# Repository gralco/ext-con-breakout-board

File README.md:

A breakout board for J10 on the Librem 5.

The rigid section has an overall thickness of 1.2mm, the flex section has an overall thickness of flex section is 0.126mm, and the stiffener and its adhesive adds 0.125mm on top of the thickness of the flex.

The panels were made by PCBWay, if you would like to order these yourself then you can use their product number W159429AS1D27 to reorder the same panel.

The FPC connector used is either Panasonic AXT624124 or OK-06M024-04.

Here is a photo of a v0.6 panel:

Here is a photo of the rigid-flex board mounted inside a Librem 5, using the center M.2 cover screw to fasten the rigid section down:

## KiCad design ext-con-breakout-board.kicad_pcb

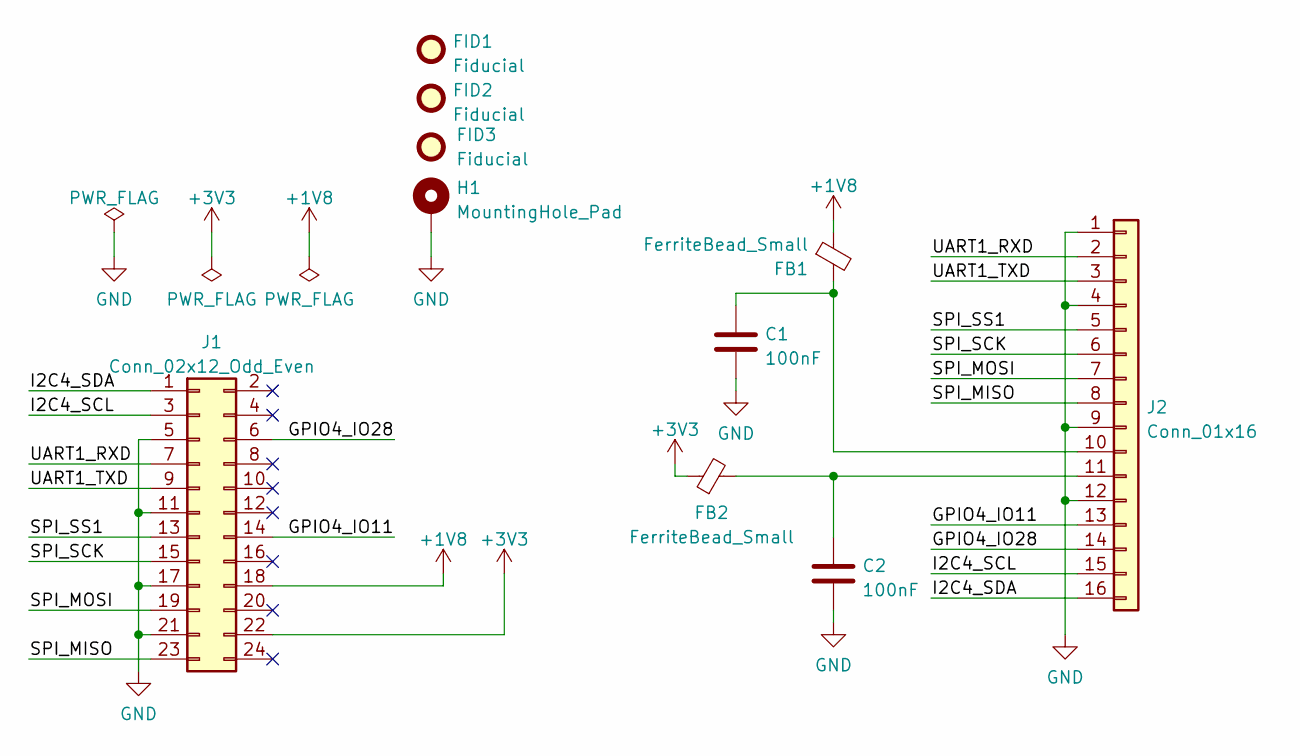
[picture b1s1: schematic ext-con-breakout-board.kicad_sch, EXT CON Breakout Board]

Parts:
C1, C2: 100nF; C_0402_1005Metric
FB1, FB2: FerriteBead_Small; L_0402_1005Metric
FID1, FID2, FID3: Fiducial; Fiducial_0.5mm_Mask1mm
H1: MountingHole_Pad; MountingHole_1.7mm_M1.4_Pad
J1: Conn_02x12_Odd_Even; AXT624124; MFG Part Num AXT624124
J2: Conn_01x16; PinHeader_1x16_P2.54mm_Vertical

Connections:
+1V8: FB1.1, J1.18
+3V3: FB2.1, J1.22
/GPIO4_IO11: J1.14, J2.13
/GPIO4_IO28: J1.6, J2.14
/I2C4_SCL: J1.3, J2.15
/I2C4_SDA: J1.1, J2.16
/SPI_MISO: J1.23, J2.8
/SPI_MOSI: J1.19, J2.7
/SPI_SCK: J1.15, J2.6
/SPI_SS1: J1.13, J2.5
/UART1_RXD: J1.7, J2.2
/UART1_TXD: J1.9, J2.3
GND: C1.2, C2.2, H1.1, J1.5, J1.11, J1.17, J1.21, J2.1, J2.4, J2.9, J2.12
unnamed: C1.1, FB1.2, J2.10
unnamed: C2.1, FB2.2, J2.11

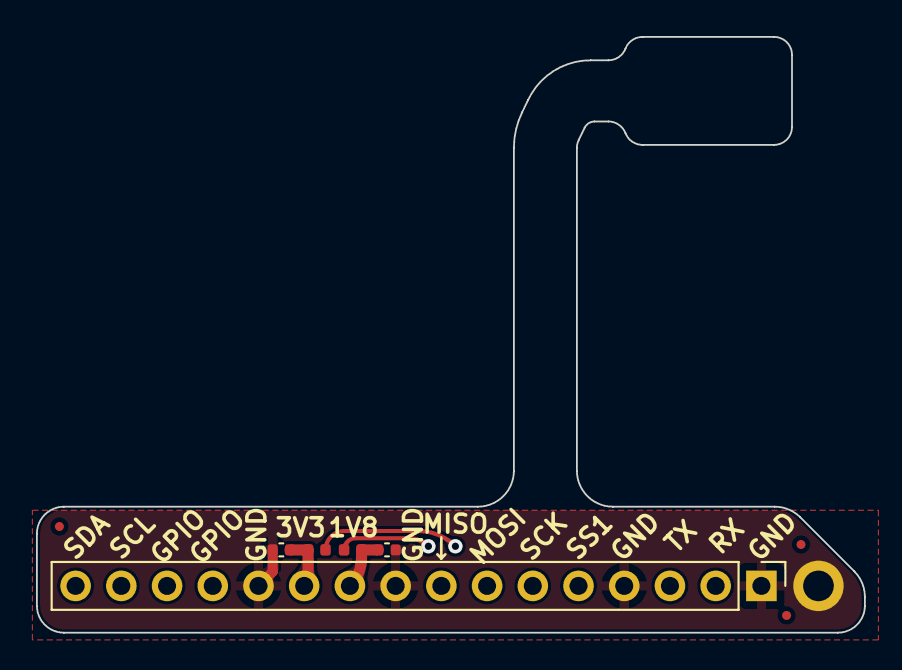
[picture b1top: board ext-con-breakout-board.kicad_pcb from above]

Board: 4 copper layers, 46.0 x 33.1 mm, 10 parts (0 on the bottom side), 15 nets.

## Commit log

2022-07-13 Add LICENSE
2022-07-13 Add the start of the project
2022-07-16 Begin fanning out the nets near the FPC connector
2022-07-19 Adjust the edge cuts based on the space available on the phone
    Rev v1.0.6 of the phone has a plastic bracket on the mid-frame which
    joins the WiFi tab holder section to the section above the smartcard
    slot. This piece bridges over the testi points and has holes where the
    test points are located.
    The intent of the edge cut design in this commit is to snake around the
    plastic mid-frame that bridges between the two sections as was
2022-07-20 Route the remaining portion of the FPC section and add the rigid section
    The rigid section has a mounting hole which lines up with the center
    screw that holds the M.2 cover in place. This will allow the board to be
    mounted to the back of the phone.
    Extra flex length was given to ensure enough distance to reach the
    position where the rigid section will be mounted. The drawings on the
    User.1 layer shows where the plastic obstacles are as well as the
2022-07-20 Make the board 4 layers and move the flex copper to the inner layers
    The 0402 caps and ferrite beads and their traces have to remain on the
    F.Cu layer.
    This commit was accomplished by having to manually edit the .kicad_pcb
    text file in order to move the previous F.Cu & B.Cu layers to becoming
    In1.Cu & In2.Cu.
    Also add notes regarding where the rigid section is, where the flex
2022-07-20 Export the manufacturing files (gerbers and PDF)
    Add fab notes on the User.Comments layer. Include a general stackup
    guide image in the PDF fabrication drawing.
    Re-centered the whole board on the canvas. The vias on the flex section
    have to be set as "buried" vias going from In1.Cu to In2.Cu in order to
    get the correct gerber export.
2022-07-20 Fix the SPI_SCK and SPI_SS1 traces having slight kinks on the straight long flex section
    Re-export the gerbers after this fix is applied.
2022-07-21 Fix the spelling of polyimide in the stackup guide
2022-07-25 Add a graphic which clearly shows the rigid, flex, and stiffener sections to the fab drawing
    Add the fab drawing in this commit.
    Include the height and width dimensions of the board in the fab drawing
    and the comments auxilary layer of the gerbers.
2022-07-25 Update the fab drawing to show the dimensions of the rigid section as well as the width of the kapton stiffener area
2022-08-24 Add the manufacturer's (PCBWay's) panel gerbers
2022-08-24 Add photos of the panel and the board inside a phone
    Add an image of the final stackup and the answered engineering queries
    from PCBWay.
2023-01-04 Swap the 3V3 and 1V8 labels on the silkscreen
2023-01-05 Shrink the flex section by 3.5mm, increment the version to v0.6, re-export the fabrication drawing (PDF), and re-export the gerbers
    Also export the schematic as a PDF.
2023-02-06 Replace the inside_phone.png photo with an edited one which swaps the 1V8 and 3V3 silkscreen markings to reduce the likelihood of this mistake being referenced
2023-02-06 Replace the PCBWay product number in the README to use the one for v0.6
2023-02-06 Specify that the photo of the panel is a v0.5 panel, the panel for v0.6 is a 2*3 array
2023-02-13 Update the project to use the KiCad 7.0 format
2023-02-23 Add the v0.6 panelized gerbers from PCBWay
2023-02-27 Add the v0.6 panelized ODB++ file from PCBWay
2023-04-03 Update the README to mention that the Panasonic AXT624124 FPC connector is an option
2023-04-04 Update the photo of the panel to use the v0.6 one
2023-04-23 Add teardrops to the 0402 pads, add GND trace from C2 to the through hole pin, make the FPC connector part number be Panasonic AXT624124, add a 3D model for the FPC connector, fix and wave all DRCs o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
2023-09-27 Add a silkscreen arrow pointing at the MISO pin
    Add a third fiducial. Reduce the thermal relief gap to 0.428mm so that
    the GND pins can have four spokes connecting to the copper pour on
    ln2.Cu.
    Fix the hatched lines drawn in the "Flex Section" on the User.Comments
    layer.
2024-05-25 Update project to KiCad 8 and use built-in teardrops
    * Add IPC-2581 file
2024-11-08 README: The panel is for v0.6
2024-11-08 README: Update the PCBWay product number for v0.6
2025-03-01 Update the project to KiCad 9.0 and fix the GND hatched copper on layer 2
    Create a .kicad_jobset file for exporting manufacturing outputs.

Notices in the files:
ext-con-breakout-board.kicad_pcb:
GNU GPLv3+
Purism SPC GPLv3+
